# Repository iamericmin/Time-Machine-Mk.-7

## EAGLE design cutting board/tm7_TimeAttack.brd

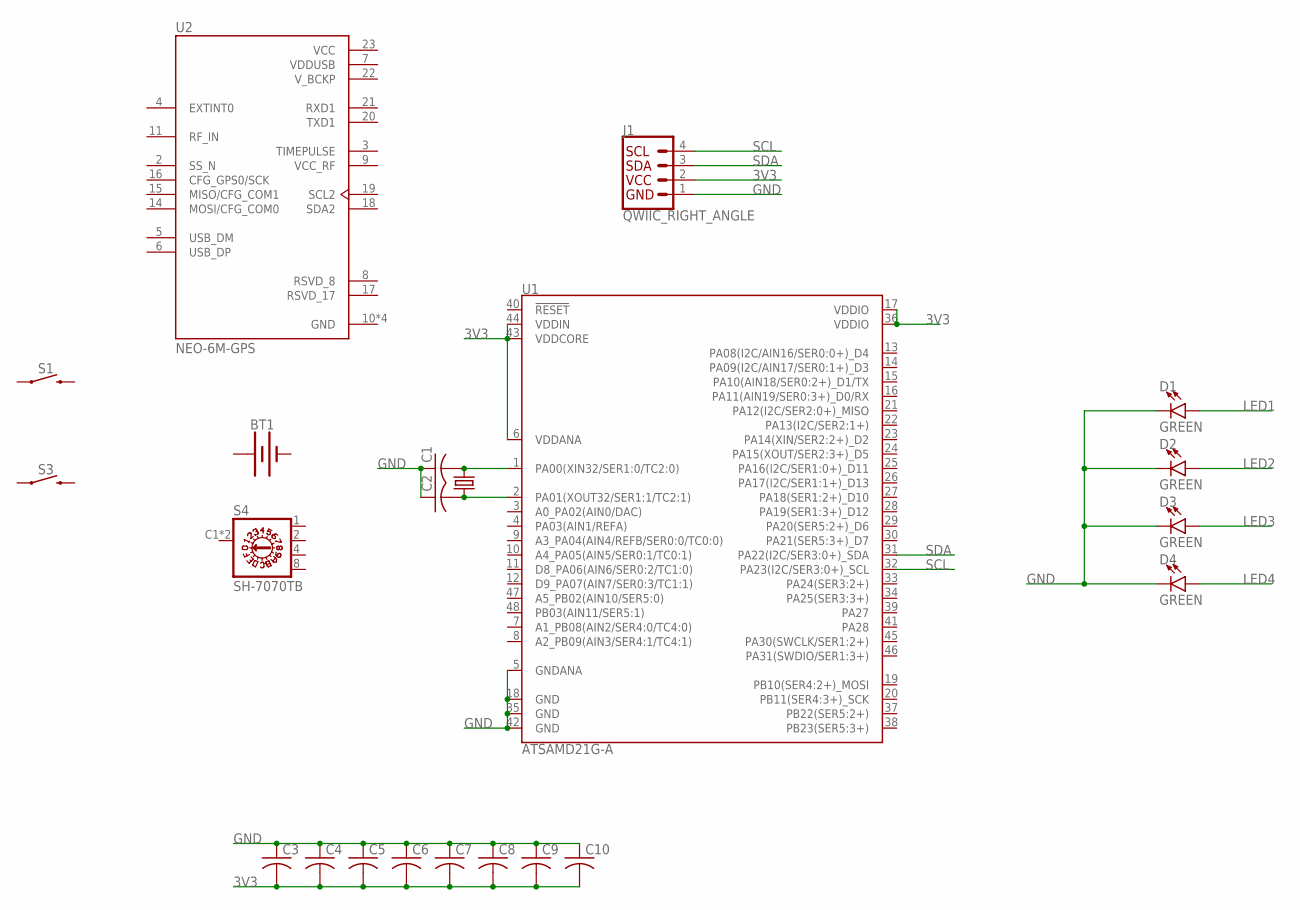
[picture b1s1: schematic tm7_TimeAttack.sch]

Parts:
BT1: BATTERY-20MM_SMD_4LEGS_OVERPASTE_INNER; BATTCON_20MM_4LEGS_OVERPASTE_INNER
C1, C2, C3, C4, C5, C6, C7, C8, C9, C10: C-USC0402; C0402
D1, D2, D3, D4: GREEN; LED-1206
J1: QWIIC_RIGHT_ANGLE; JST04_1MM_RA
S1, S3: MOMENTARY-SWITCH-SPST-SMD-6.2MM-TALL; TACTILE_SWITCH_SMD_6.2MM_TALL
S4: SH-7070TB; SH-7070B
U1: ATSAMD21G-A; TQFP-48
U2: NEO-6M-GPS; XCVR_NEO-6M-GPS
Y1: 32.768kHz; CRYSTAL-SMD-3.2X1.5MM

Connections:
3V3: C3.2, C4.2, C5.2, C6.2, C7.2, C8.2, C9.2, C10.2, J1.2, U1.6 (VDDANA), U1.17 (VDDIO), U1.36 (VDDIO), U1.43 (VDDCORE), U1.44 (VDDIN)
+: BT1.1 (+)
-: BT1.2 (-)
GND: C1.1, C2.1, C3.1, C4.1, C5.1, C6.1, C7.1, C8.1, C9.1, C10.1, D1.C, D2.C, D3.C, D4.C, J1.1, U1.5 (GNDANA), U1.18 (GND), U1.35 (GND), U1.42 (GND), U2.10 (GND), U2.12 (GND), U2.13 (GND), U2.24 (GND)
LED1: D1.A
LED2: D2.A
LED3: D3.A
LED4: D4.A
unnamed: C1.2, U1.1 (PA00(XIN32/SER1:0/TC2:0)), Y1.P$2 (2)
unnamed: C2.2, U1.2 (PA01(XOUT32/SER1:1/TC2:1)), Y1.P$1 (1)
SCL: J1.4, U1.32 (PA23(I2C/SER3:0+)_SCL)
SDA: J1.3, U1.31 (PA22(I2C/SER3:0+)_SDA)
VCC: U2.23 (VCC)
VDDUSB: U2.7 (VDDUSB)
V_BCKP: U2.22 (V_BCKP)

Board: 2 copper layers, 22 parts (15 on the bottom side), 6 nets, no tracks yet.

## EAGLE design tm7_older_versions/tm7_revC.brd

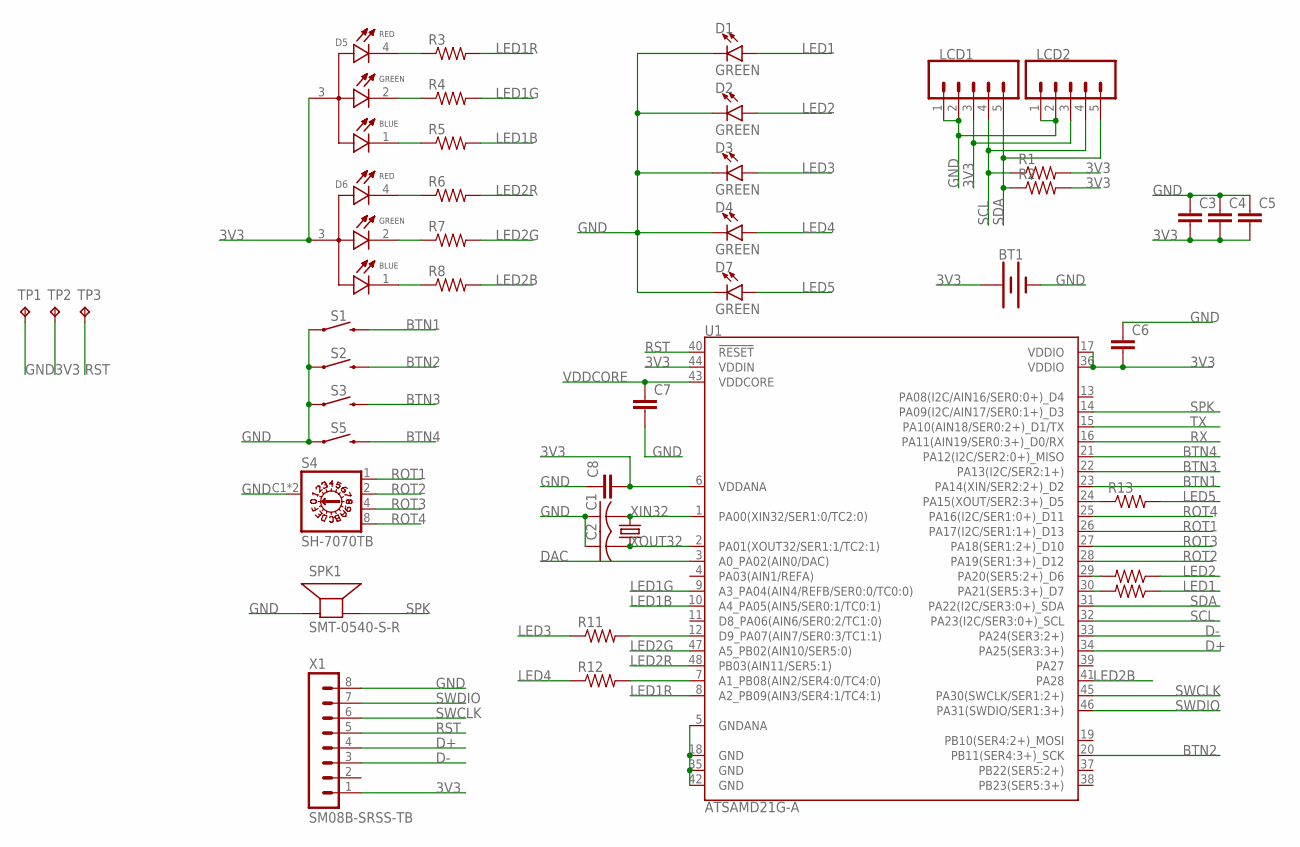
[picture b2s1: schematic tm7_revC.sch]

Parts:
BT1: BATTERY-20MM_SMD_4LEGS_OVERPASTE_INNER; BATTCON_20MM_4LEGS_OVERPASTE_INNER
C1, C2: C-USC0603; C0603
C3, C4, C5, C6, C7, C8: C-EUC0603; C0603
D1, D2, D3, D4, D7: GREEN; LED-1206
D5, D6: EAST1616RGBA3; LED_EAST1616RGBA3
LCD1, LCD2: CONN_05VERT_FEMALE_HEADER; 1X05_SMD_VERTICAL_COMBO
R1, R2, R3, R4, R5, R6, R7, R8, R9, R10, R11, R12, R13: R-US_R0603; R0603
S1, S2, S3, S5: MOMENTARY-SWITCH-SPST-SMD-6.0X3.5MM; TACTILE_SWITCH_SMD_6.0X3.5MM
S4: SH-7070TB; SH-7070B
SPK1: SMT-0540-S-R
TP1, TP2, TP3: TPTP12R; TP12R
U1: ATSAMD21G-A; TQFP-48
X1: SM08B-SRSS-TB
Y1: 32.768kHz; CRYSTAL-SMD-3.2X1.5MM

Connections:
3V3: BT1.1 (+), C3.2, C4.2, C5.2, C6.2, C8.2, D5.3 (A), D6.3 (A), LCD1.3, LCD2.3, R1.2, R2.2, TP2.TP, U1.6 (VDDANA), U1.17 (VDDIO), U1.36 (VDDIO), U1.44 (VDDIN), X1.1
BTN1: S1.2, U1.23 (PA14(XIN/SER2:2+)_D2)
BTN2: S2.2, U1.20 (PB11(SER4:3+)_SCK)
BTN3: S3.2, U1.22 (PA13(I2C/SER2:1+))
BTN4: S5.2, U1.21 (PA12(I2C/SER2:0+)_MISO)
D+: U1.34 (PA25(SER3:3+)), X1.4
D-: U1.33 (PA24(SER3:2+)), X1.3
DAC: U1.3 (A0_PA02(AIN0/DAC))
GND: BT1.2 (-), C1.1, C2.1, C3.1, C4.1, C5.1, C6.1, C7.2, C8.1, D1.C, D2.C, D3.C, D4.C, D7.C, LCD1.1, LCD1.2, LCD2.1, LCD2.2, S1.1, S2.1, S3.1, S4.C1 (C), S4.C2 (C), S5.1, SPK1.- (+), TP1.TP, U1.5 (GNDANA), U1.18 (GND), U1.35 (GND), U1.42 (GND), X1.8
LED1: D1.A, R9.1
LED1B: R5.2, U1.10 (A4_PA05(AIN5/SER0:1/TC0:1))
LED1G: R4.2, U1.9 (A3_PA04(AIN4/REFB/SER0:0/TC0:0))
LED1R: R3.2, U1.8 (A2_PB09(AIN3/SER4:1/TC4:1))
LED2: D2.A, R10.1
LED2B: R8.2, U1.41 (PA28)
LED2G: R7.2, U1.47 (A5_PB02(AIN10/SER5:0))
LED2R: R6.2, U1.48 (PB03(AIN11/SER5:1))
LED3: D3.A, R11.1
LED4: D4.A, R12.1
LED5: D7.A, R13.2
unnamed: R12.2, U1.7 (A1_PB08(AIN2/SER4:0/TC4:0))
unnamed: R11.2, U1.12 (D9_PA07(AIN7/SER0:3/TC1:1))
unnamed: R9.2, U1.30 (PA21(SER5:3+)_D7)
unnamed: R10.2, U1.29 (PA20(SER5:2+)_D6)
unnamed: D5.4 (R_C), R3.1
unnamed: D5.2 (G_C), R4.1
unnamed: D5.1 (B_C), R5.1
unnamed: D6.4 (R_C), R6.1
unnamed: D6.2 (G_C), R7.1
unnamed: D6.1 (B_C), R8.1
unnamed: R13.1, U1.24 (PA15(XOUT/SER2:3+)_D5)
ROT1: S4.1, U1.26 (PA17(I2C/SER1:1+)_D13)
ROT2: S4.2, U1.28 (PA19(SER1:3+)_D12)
ROT3: S4.4, U1.27 (PA18(SER1:2+)_D10)
ROT4: S4.8, U1.25 (PA16(I2C/SER1:0+)_D11)
RST: TP3.TP, U1.40 (!RESET!), X1.5
RX: U1.16 (PA11(AIN19/SER0:3+)_D0/RX)
SCL: LCD1.4, LCD2.4, R1.1, U1.32 (PA23(I2C/SER3:0+)_SCL)
SDA: LCD1.5, LCD2.5, R2.1, U1.31 (PA22(I2C/SER3:0+)_SDA)
SPK: SPK1.+ (-), U1.14 (PA09(I2C/AIN17/SER0:1+)_D3)
SWCLK: U1.45 (PA30(SWCLK/SER1:2+)), X1.6
SWDIO: U1.46 (PA31(SWDIO/SER1:3+)), X1.7
TX: U1.15 (PA10(AIN18/SER0:2+)_D1/TX)
VDDCORE: C7.1, U1.43 (VDDCORE)
XIN32: C1.2, U1.1 (PA00(XIN32/SER1:0/TC2:0)), Y1.P$2 (2)
XOUT32: C2.2, U1.2 (PA01(XOUT32/SER1:1/TC2:1)), Y1.P$1 (1)

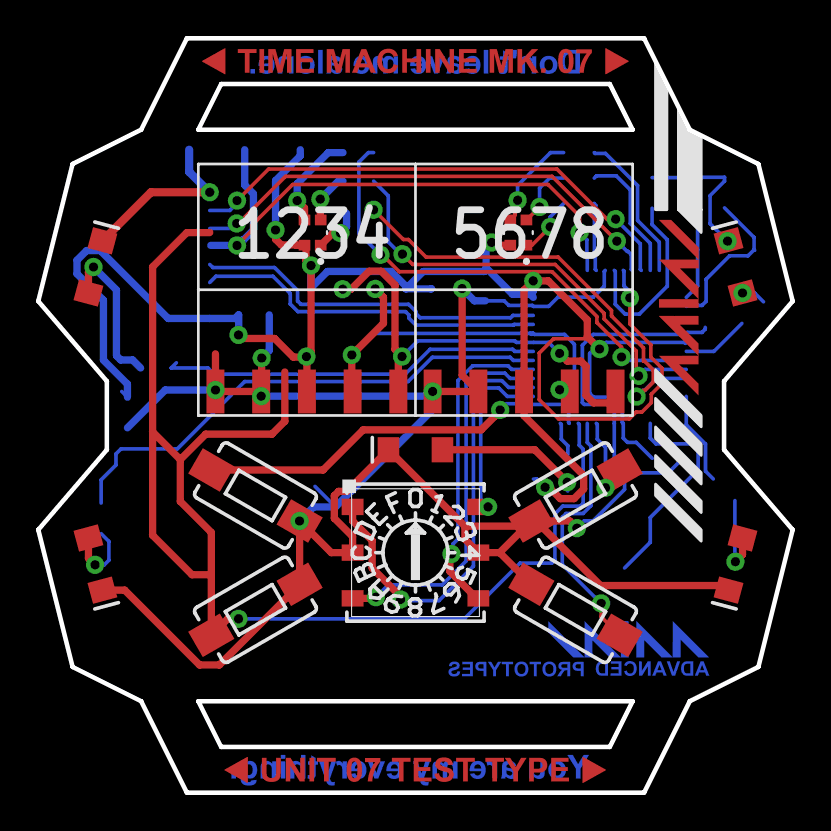
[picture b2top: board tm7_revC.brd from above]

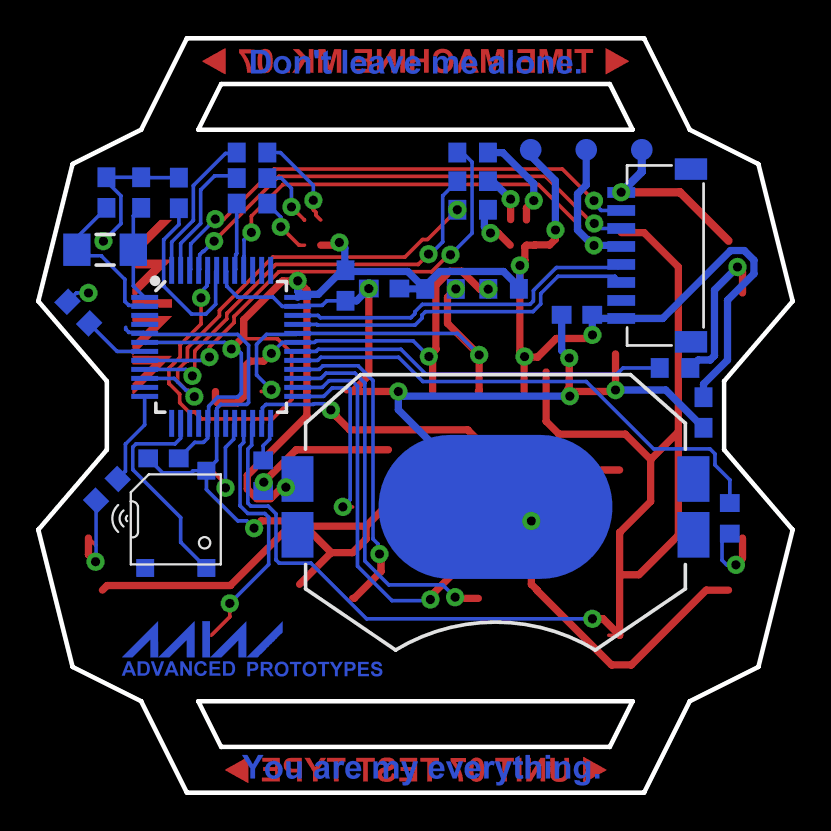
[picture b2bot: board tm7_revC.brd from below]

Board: 2 copper layers, 41.9 x 41.9 mm, 43 parts (29 on the bottom side), 43 nets.

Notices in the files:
parts and their libraries:
SparkFun-Switches: Licensing: Creative Commons ShareAlike 4.0 International - https://creativecommons.org/licenses/by-sa/4.0
